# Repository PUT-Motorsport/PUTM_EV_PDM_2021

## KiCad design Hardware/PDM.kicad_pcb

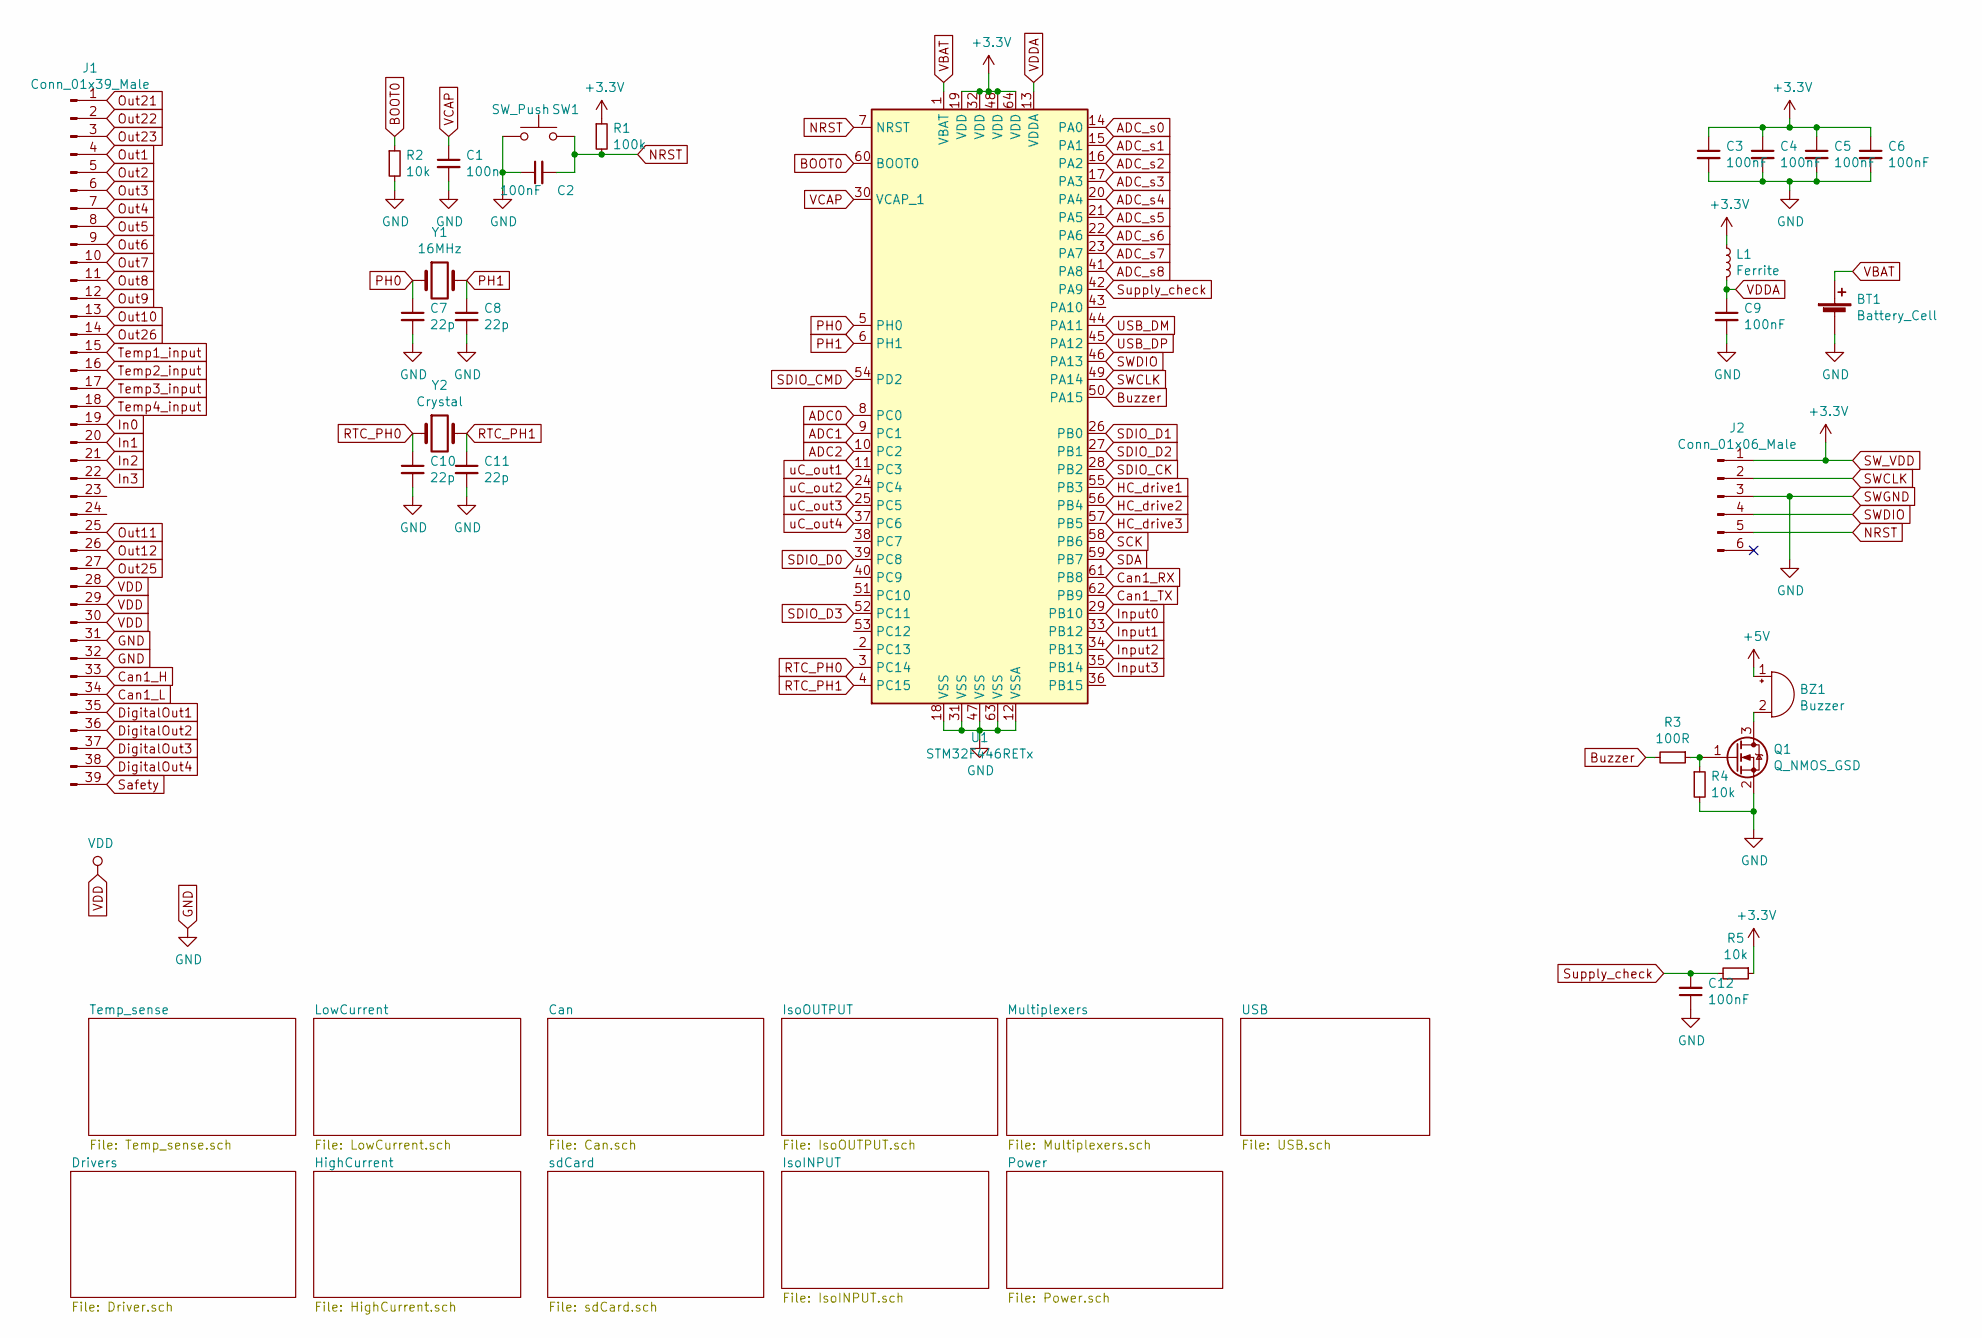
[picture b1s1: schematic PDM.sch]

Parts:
BT1: Battery_Cell; BatteryHolder_Keystone_103_1x20mm
BZ1: Buzzer; Buzzer_TDK_PS1240P02BT_D12.2mm_H6.5mm
C1: 100n; C_0603_1608Metric
C2, C3, C4, C5, C6, C9, C12: 100nF; C_0603_1608Metric
C7, C8, C10, C11: 22p; C_0603_1608Metric
J1: Conn_01x39_Male; 39pinFCI_ECU
J2: Conn_01x06_Male; PinHeader_1x06_P2.54mm_Vertical
L1: Ferrite; L_0805_2012Metric
Q1: Q_NMOS_GSD; SOT-23
R1: 100k; R_0603_1608Metric
R2, R4, R5: 10k; R_0603_1608Metric
R3: 100R; R_0603_1608Metric
SW1: SW_Push; SW_PUSH_6mm_H5mm
U1: STM32F446RETx; LQFP-64_10x10mm_P0.5mm
Y1: 16MHz; Crystal_SMD_HC49-SD
Y2: Crystal; Crystal_SMD_HC49-SD

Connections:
+5V: BZ1.1 (-); also elsewhere on the board
ADC0: U1.8 (PC0); also elsewhere on the board
ADC1: U1.9 (PC1); also elsewhere on the board
ADC2: U1.10 (PC2); also elsewhere on the board
ADC_s0: U1.14 (PA0); also elsewhere on the board
ADC_s1: U1.15 (PA1); also elsewhere on the board
ADC_s2: U1.16 (PA2); also elsewhere on the board
ADC_s3: U1.17 (PA3); also elsewhere on the board
ADC_s4: U1.20 (PA4); also elsewhere on the board
ADC_s5: U1.21 (PA5); also elsewhere on the board
ADC_s6: U1.22 (PA6); also elsewhere on the board
ADC_s7: U1.23 (PA7); also elsewhere on the board
ADC_s8: U1.41 (PA8); also elsewhere on the board
BOOT0: R2.1, U1.60 (BOOT0)
Buzzer: R3.2, U1.50 (PA15)
Can1_H: J1.33; also elsewhere on the board
Can1_L: J1.34; also elsewhere on the board
Can1_RX: U1.61 (PB8); also elsewhere on the board
Can1_TX: U1.62 (PB9); also elsewhere on the board
DigitalOut1: J1.35; also elsewhere on the board
DigitalOut2: J1.36; also elsewhere on the board
DigitalOut3: J1.37; also elsewhere on the board
DigitalOut4: J1.38; also elsewhere on the board
GND: BT1.2 (-), C1.2, C2.1, C3.2, C4.2, C5.2, C6.2, C7.2, C8.2, C9.2, C10.2, C11.2, C12.1, J1.31, J1.32, J2.3, Q1.2 (S), R2.2, R4.2, SW1.1, U1.12 (VSSA), U1.18 (VSS), U1.31 (VSS), U1.47 (VSS), U1.63 (VSS); also elsewhere on the board
HC_drive1: U1.55 (PB3); also elsewhere on the board
HC_drive2: U1.56 (PB4); also elsewhere on the board
HC_drive3: U1.57 (PB5); also elsewhere on the board
In0: J1.19; also elsewhere on the board
In1: J1.20; also elsewhere on the board
In2: J1.21; also elsewhere on the board
In3: J1.22; also elsewhere on the board
Input0: U1.29 (PB10); also elsewhere on the board
Input1: U1.33 (PB12); also elsewhere on the board
Input2: U1.34 (PB13); also elsewhere on the board
Input3: U1.35 (PB14); also elsewhere on the board
NRST: C2.2, J2.5, R1.2, SW1.2, U1.7 (NRST)
unnamed: BZ1.2 (+), Q1.3 (D)
unnamed: Q1.1 (G), R3.1, R4.1
Out1: J1.4; also elsewhere on the board
Out2: J1.5; also elsewhere on the board
Out3: J1.6; also elsewhere on the board
Out4: J1.7; also elsewhere on the board
Out5: J1.8; also elsewhere on the board
Out6: J1.9; also elsewhere on the board
Out7: J1.10; also elsewhere on the board
Out8: J1.11; also elsewhere on the board
Out9: J1.12; also elsewhere on the board
Out10: J1.13; also elsewhere on the board
Out11: J1.25; also elsewhere on the board
Out12: J1.26; also elsewhere on the board
Out21: J1.1; also elsewhere on the board
Out22: J1.2; also elsewhere on the board
Out23: J1.3; also elsewhere on the board
Out25: J1.27; also elsewhere on the board
Out26: J1.14; also elsewhere on the board
PH0: C7.1, U1.5 (PH0), Y1.1
PH1: C8.1, U1.6 (PH1), Y1.2
RTC_PH0: C10.1, U1.3 (PC14), Y2.1
RTC_PH1: C11.1, U1.4 (PC15), Y2.2
SCK: U1.58 (PB6); also elsewhere on the board
SDA: U1.59 (PB7); also elsewhere on the board
SDIO_CK: U1.28 (PB2); also elsewhere on the board
SDIO_CMD: U1.54 (PD2); also elsewhere on the board
SDIO_D0: U1.39 (PC8); also elsewhere on the board
SDIO_D1: U1.26 (PB0); also elsewhere on the board
SDIO_D2: U1.27 (PB1); also elsewhere on the board
SDIO_D3: U1.52 (PC11); also elsewhere on the board
SWCLK: J2.2, U1.49 (PA14)
SWDIO: J2.4, U1.46 (PA13)
SW_VDD: C3.1, C4.1, C5.1, C6.1, J2.1, L1.1, R1.1, R5.1, U1.19 (VDD), U1.32 (VDD), U1.48 (VDD), U1.64 (VDD); also elsewhere on the board
Safety: J1.39; also elsewhere on the board
Supply_check: C12.2, R5.2, U1.42 (PA9)
Temp1_input: J1.15; also elsewhere on the board
Temp2_input: J1.16; also elsewhere on the board
Temp3_input: J1.17; also elsewhere on the board
Temp4_input: J1.18; also elsewhere on the board
USB_DM: U1.44 (PA11); also elsewhere on the board
USB_DP: U1.45 (PA12); also elsewhere on the board
VBAT: BT1.1 (+), U1.1 (VBAT)
VCAP: C1.1, U1.30 (VCAP_1)
VDD: J1.28, J1.29, J1.30; also elsewhere on the board
VDDA: C9.1, L1.2, U1.13 (VDDA)
uC_out1: U1.11 (PC3); also elsewhere on the board
uC_out2: U1.24 (PC4); also elsewhere on the board
uC_out3: U1.25 (PC5); also elsewhere on the board
uC_out4: U1.37 (PC6); also elsewhere on the board

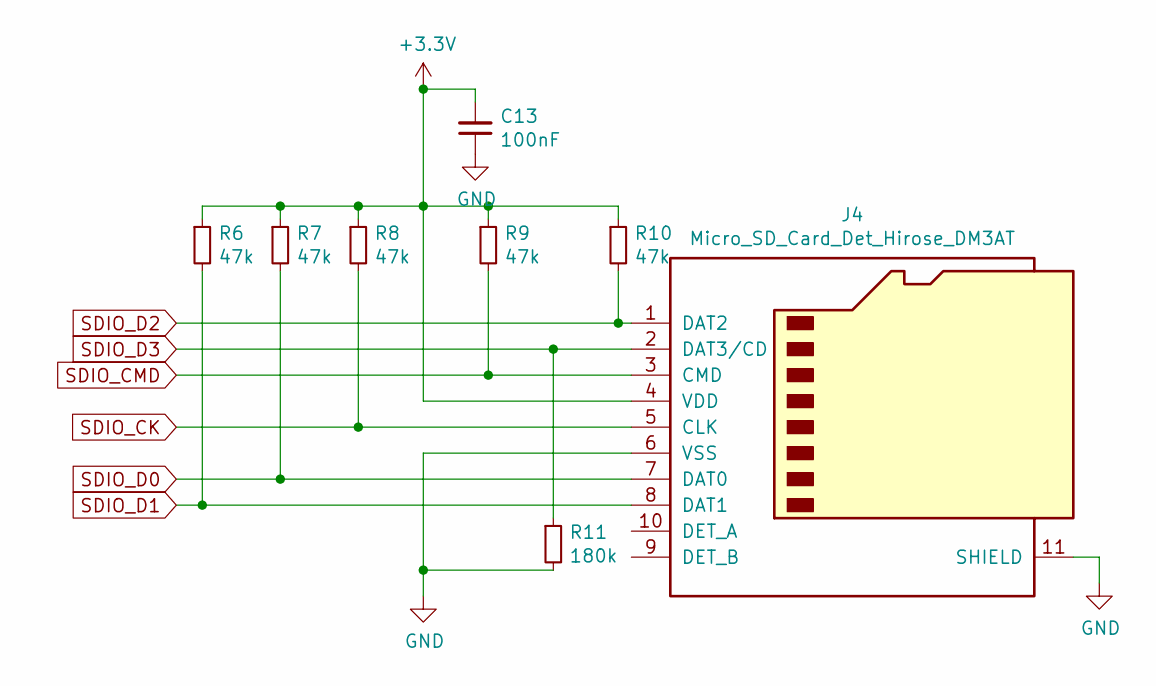
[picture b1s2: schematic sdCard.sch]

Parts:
C13: 100nF; C_0603_1608Metric
J4: Micro_SD_Card_Det_Hirose_DM3AT; microSD_HC_Hirose_DM3AT-SF-PEJM5
R6, R7, R8, R9, R10: 47k; R_0603_1608Metric
R11: 180k; R_0603_1608Metric

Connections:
GND: C13.1, J4.6 (VSS), J4.11 (SHIELD), R11.2; also elsewhere on the board
SDIO_CK: J4.5 (CLK), R8.2; also elsewhere on the board
SDIO_CMD: J4.3 (CMD), R9.2; also elsewhere on the board
SDIO_D0: J4.7 (DAT0), R7.2; also elsewhere on the board
SDIO_D1: J4.8 (DAT1), R6.2; also elsewhere on the board
SDIO_D2: J4.1 (DAT2), R10.2; also elsewhere on the board
SDIO_D3: J4.2 (DAT3/CD), R11.1; also elsewhere on the board
SW_VDD: C13.2, J4.4 (VDD), R6.1, R7.1, R8.1, R9.1, R10.1; also elsewhere on the board

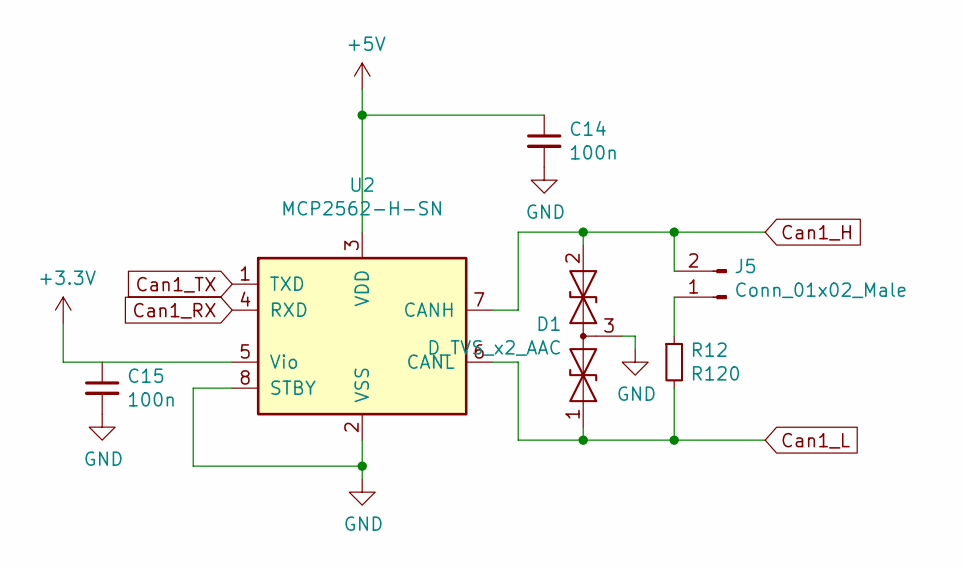
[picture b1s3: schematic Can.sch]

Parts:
C14, C15: 100n; C_0603_1608Metric
D1: D_TVS_x2_AAC; SOT-23
J5: Conn_01x02_Male; PinHeader_1x02_P2.54mm_Vertical
R12: R120; R_0603_1608Metric
U2: MCP2562-H-SN; SOIC-8_3.9x4.9mm_P1.27mm

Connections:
+5V: C14.1, U2.3 (VDD); also elsewhere on the board
Can1_H: D1.2 (A2), J5.2, U2.7 (CANH); also elsewhere on the board
Can1_L: D1.1 (A1), R12.2, U2.6 (CANL); also elsewhere on the board
Can1_RX: U2.4 (RXD); also elsewhere on the board
Can1_TX: U2.1 (TXD); also elsewhere on the board
GND: C14.2, C15.2, D1.3 (common), U2.2 (VSS), U2.8 (STBY); also elsewhere on the board
unnamed: J5.1, R12.1
SW_VDD: U2.5 (Vio); also elsewhere on the board

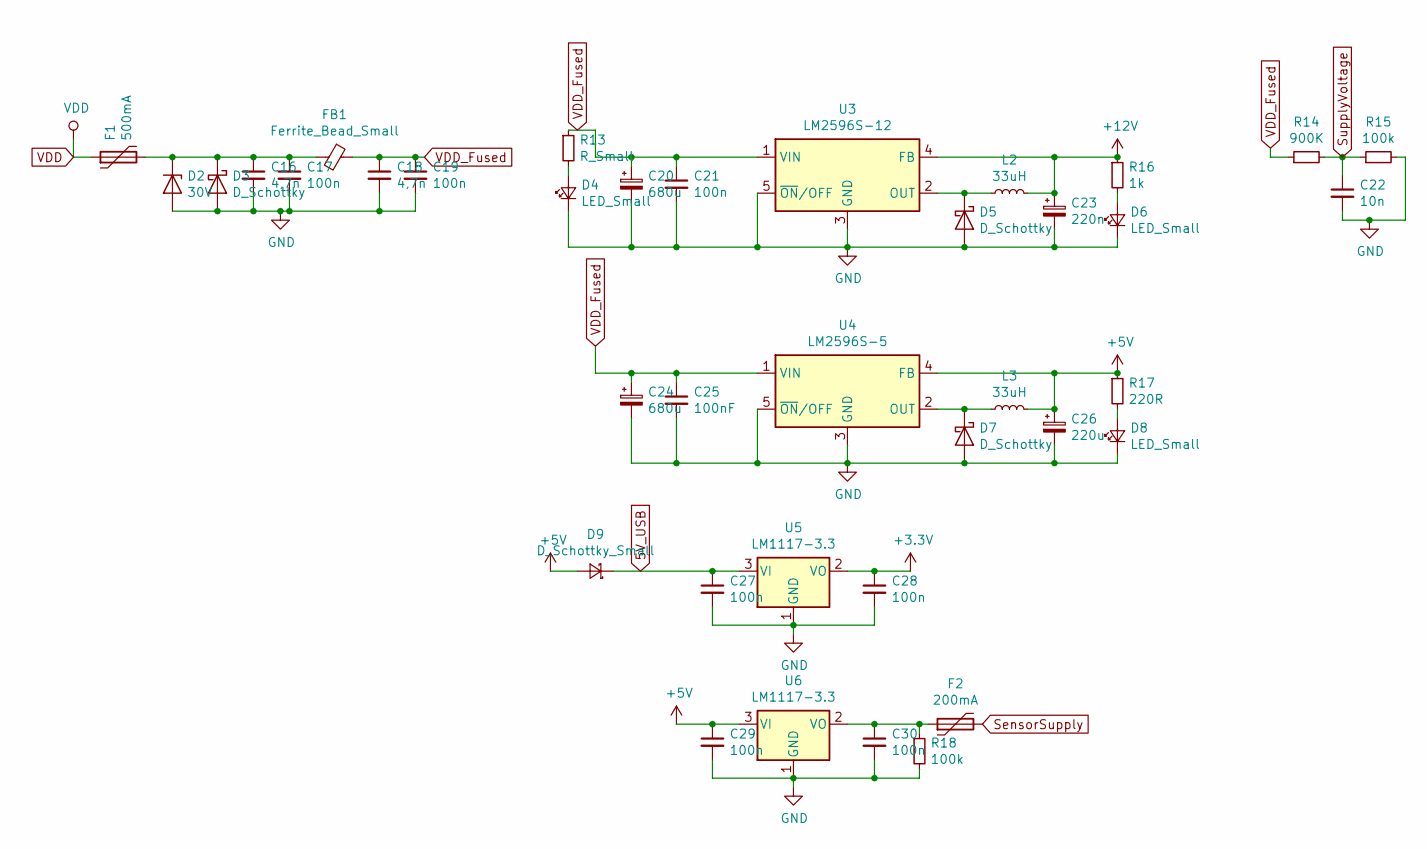
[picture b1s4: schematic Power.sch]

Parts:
C16, C18: 4,7n; C_0603_1608Metric
C17, C19, C21, C27, C28, C29, C30: 100n; C_0603_1608Metric
C20, C24: 680u; CP_Elec_8x10.5
C22: 10n; C_0603_1608Metric
C23: 220n; C_0603_1608Metric
C25: 100nF; C_0603_1608Metric
C26: 220u; CP_Elec_6.3x5.8
D2: 30V; D_SMB
D3, D5, D7: D_Schottky; D_SMB
D4, D6, D8: LED_Small; D_0805_2012Metric
D9: D_Schottky_Small; D_SMB
F1: 500mA; Fuse_1812_4532Metric
F2: 200mA; Fuse_1812_4532Metric
FB1: Ferrite_Bead_Small; L_1206_3216Metric
L2, L3: 33uH; L_12x12mm_H8mm
R13: R_Small; R_0603_1608Metric
R14: 900K; R_0603_1608Metric
R15, R18: 100k; R_0603_1608Metric
R16: 1k; R_0603_1608Metric
R17: 220R; R_0603_1608Metric
U3: LM2596S-12; TO-263-5_TabPin3
U4: LM2596S-5; TO-263-5_TabPin3
U5, U6: LM1117-3.3; SOT-223-3_TabPin2

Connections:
5V_USB: C27.1, D9.1 (K), U5.3 (VI); also elsewhere on the board
+5V: C26.1, C29.1, D9.2 (A), L3.2, R17.1, U4.4 (FB), U6.3 (VI); also elsewhere on the board
+12V: C23.1, L2.2, R16.1, U3.4 (FB); also elsewhere on the board
GND: C16.2, C17.2, C18.2, C19.2, C20.2, C21.2, C22.2, C23.2, C24.2, C25.2, C26.2, C27.2, C28.2, C29.2, C30.2, D2.2 (A), D3.2 (A), D4.1 (K), D5.2 (A), D6.1 (K), D7.2 (A), D8.1 (K), R15.2, R18.2, U3.3 (GND), U3.5 (~ON~/OFF), U4.3 (GND), U4.5 (~ON~/OFF), U5.1 (GND), U6.1 (GND); also elsewhere on the board
unnamed: C16.1, C17.1, D2.1 (K), D3.1 (K), F1.2, FB1.2
unnamed: C30.1, F2.1, R18.1, U6.2 (VO)
unnamed: D4.2 (A), R13.2
unnamed: D5.1 (K), L2.1, U3.2 (OUT)
unnamed: D6.2 (A), R16.2
unnamed: D7.1 (K), L3.1, U4.2 (OUT)
unnamed: D8.2 (A), R17.2
SW_VDD: C28.1, U5.2 (VO); also elsewhere on the board
SensorSupply: F2.2; also elsewhere on the board
SupplyVoltage: C22.1, R14.2, R15.1; also elsewhere on the board
VDD: F1.1; also elsewhere on the board
VDD_Fused: C18.1, C19.1, C20.1, C21.1, C24.1, C25.1, FB1.1, R13.1, R14.1, U3.1 (VIN), U4.1 (VIN)

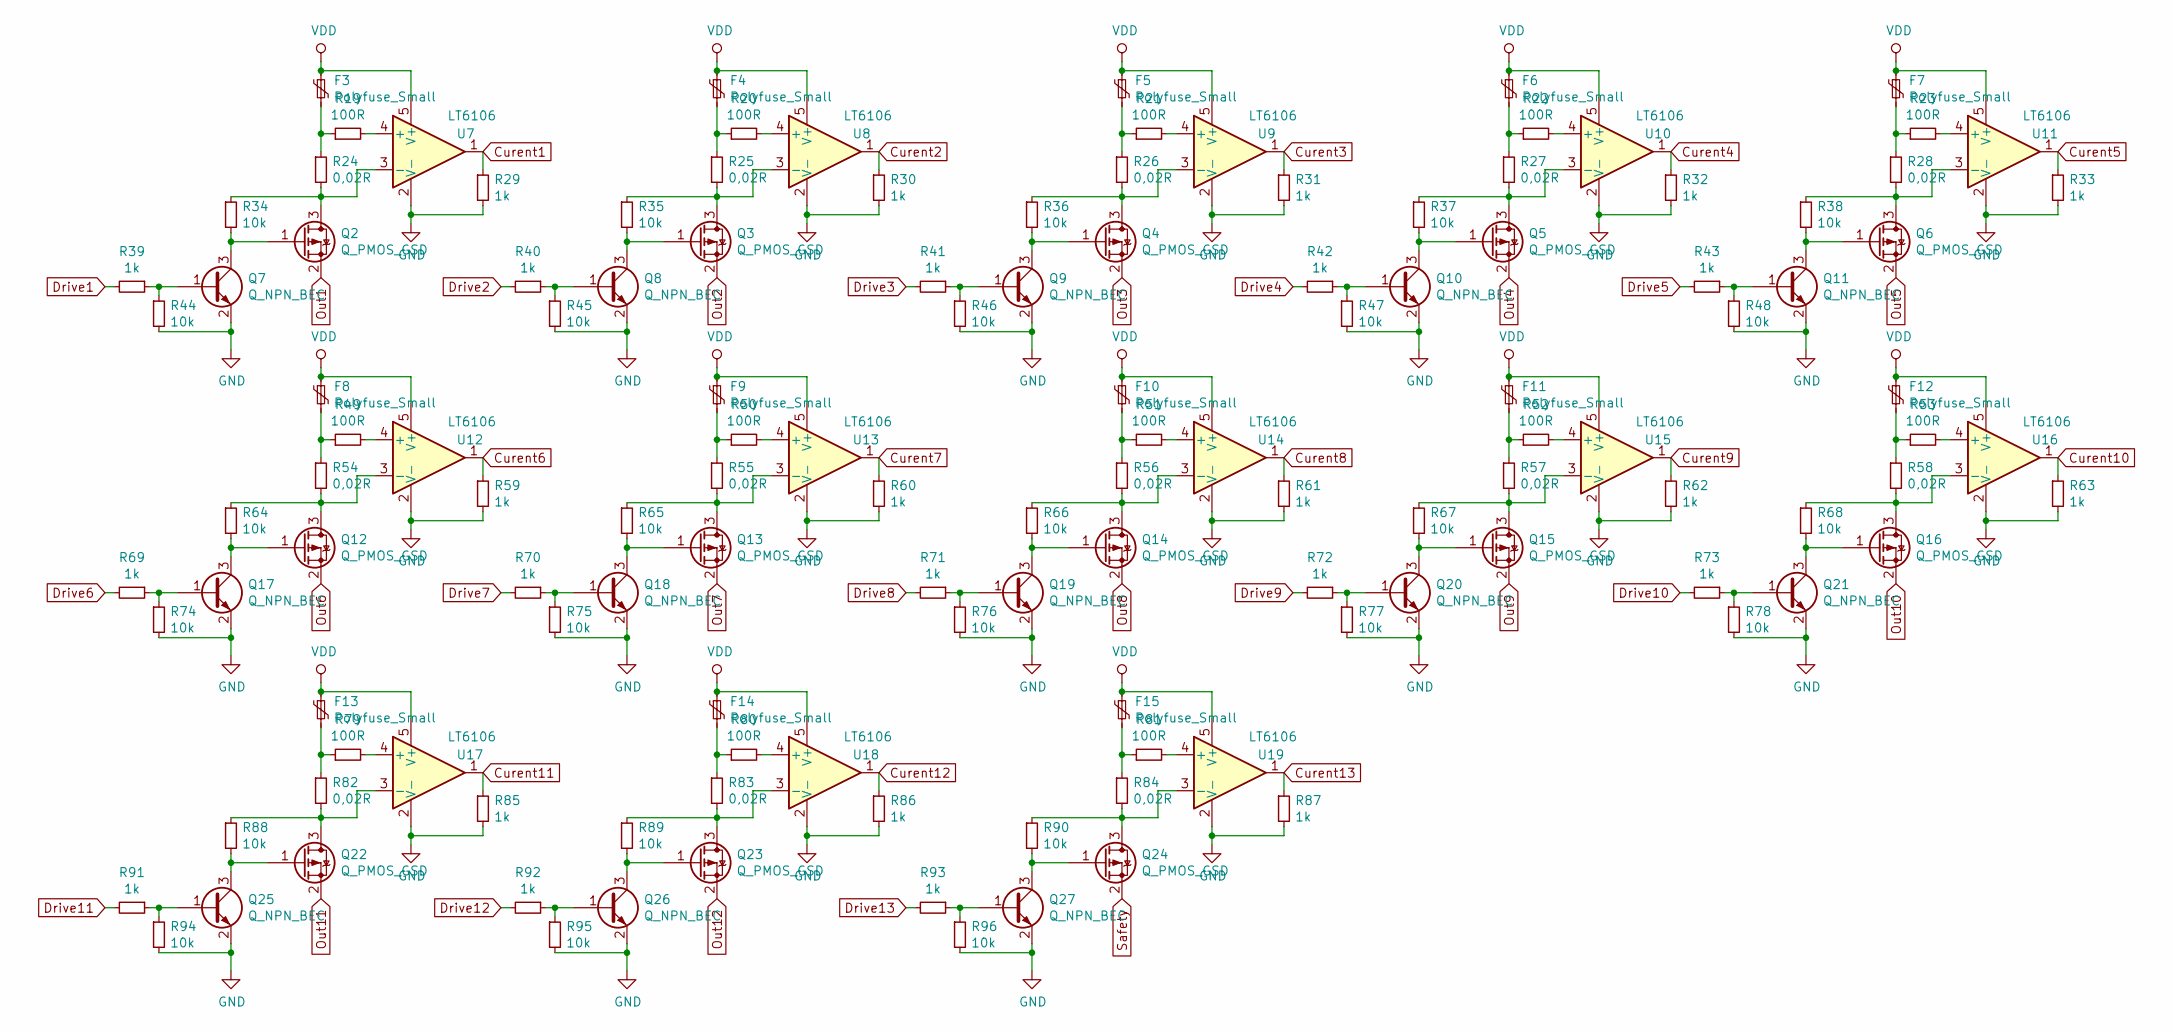
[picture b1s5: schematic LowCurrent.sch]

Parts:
F3, F4, F5, F6, F7, F8, F9, F10, F11, F12, F13, F14, F15: Polyfuse_Small; Fuse_1812_4532Metric
Q2, Q3, Q4, Q5, Q6, Q12, Q13, Q14, Q15, Q16, Q22, Q23, Q24: Q_PMOS_GSD; PowerIntegrations_SO-8
Q7, Q8, Q9, Q10, Q11, Q17, Q18, Q19, Q20, Q21: Q_NPN_BEC; SOT-23
Q25, Q26, Q27: Q_NPN_BEC; SOT-23-5
R19, R20, R21, R22, R23, R49, R50, R51, R52, R53, R79, R80, R81: 100R; R_0603_1608Metric
R24, R25, R26, R27, R28, R54, R55, R56, R57, R58, R82, R83, R84: 0,02R; R_2512_6332Metric
R29, R30, R31, R32, R33, R39, R40, R41, R42, R43, R59, R60, R61, R62, R63, R69, R70, R71, R72, R73, R85, R86, R87, R91, R92, R93: 1k; R_0603_1608Metric
R34, R35, R36, R37, R38, R44, R45, R46, R47, R48, R64, R65, R66, R67, R68, R74, R75, R76, R77, R78, R88, R89, R90, R94, R95, R96: 10k; R_0603_1608Metric
U7, U8, U9, U10, U11, U12, U13, U14, U15, U16, U17, U18, U19: LT6106; SOT-23-5

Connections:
Curent1: R29.1, U7.1; also elsewhere on the board
Curent2: R30.1, U8.1; also elsewhere on the board
Curent3: R31.1, U9.1; also elsewhere on the board
Curent4: R32.1, U10.1; also elsewhere on the board
Curent5: R33.1, U11.1; also elsewhere on the board
Curent6: R59.1, U12.1; also elsewhere on the board
Curent7: R60.1, U13.1; also elsewhere on the board
Curent8: R61.1, U14.1; also elsewhere on the board
Curent9: R62.1, U15.1; also elsewhere on the board
Curent10: R63.1, U16.1; also elsewhere on the board
Curent11: R85.1, U17.1; also elsewhere on the board
Curent12: R86.1, U18.1; also elsewhere on the board
Curent13: R87.1, U19.1; also elsewhere on the board
Drive1: R39.2; also elsewhere on the board
Drive2: R40.2; also elsewhere on the board
Drive3: R41.2; also elsewhere on the board
Drive4: R42.2; also elsewhere on the board
Drive5: R43.2; also elsewhere on the board
Drive6: R69.2; also elsewhere on the board
Drive7: R70.2; also elsewhere on the board
Drive8: R71.2; also elsewhere on the board
Drive9: R72.2; also elsewhere on the board
Drive10: R73.2; also elsewhere on the board
Drive11: R91.2; also elsewhere on the board
Drive12: R92.2; also elsewhere on the board
Drive13: R93.2; also elsewhere on the board
GND: Q7.2 (E), Q8.2 (E), Q9.2 (E), Q10.2 (E), Q11.2 (E), Q17.2 (E), Q18.2 (E), Q19.2 (E), Q20.2 (E), Q21.2 (E), Q25.2 (E), Q26.2 (E), Q27.2 (E), R29.2, R30.2, R31.2, R32.2, R33.2, R44.2, R45.2, R46.2, R47.2, R48.2, R59.2, R60.2, R61.2, R62.2, R63.2, R74.2, R75.2, R76.2, R77.2, R78.2, R85.2, R86.2, R87.2, R94.2, R95.2, R96.2, U7.2 (V-), U8.2 (V-), U9.2 (V-), U10.2 (V-), U11.2 (V-), U12.2 (V-), U13.2 (V-), U14.2 (V-), U15.2 (V-), U16.2 (V-), U17.2 (V-), U18.2 (V-), U19.2 (V-); also elsewhere on the board
unnamed: F3.2, R19.1, R24.1
unnamed: F4.2, R20.1, R25.1
unnamed: F5.2, R21.1, R26.1
unnamed: F6.2, R22.1, R27.1
unnamed: F7.2, R23.1, R28.1
unnamed: F8.2, R49.1, R54.1
unnamed: F9.2, R50.1, R55.1
unnamed: F10.2, R51.1, R56.1
unnamed: F11.2, R52.1, R57.1
unnamed: F12.2, R53.1, R58.1
unnamed: F13.2, R79.1, R82.1
unnamed: F14.2, R80.1, R83.1
unnamed: F15.2, R81.1, R84.1
unnamed: Q2.1 (G), Q7.3 (C), R34.2
unnamed: Q2.3 (D), R24.2, R34.1, U7.3 (-)
unnamed: Q3.1 (G), Q8.3 (C), R35.2
unnamed: Q3.3 (D), R25.2, R35.1, U8.3 (-)
unnamed: Q4.1 (G), Q9.3 (C), R36.2
unnamed: Q4.3 (D), R26.2, R36.1, U9.3 (-)
unnamed: Q5.3 (D), R27.2, R37.1, U10.3 (-)
unnamed: Q6.3 (D), R28.2, R38.1, U11.3 (-)
unnamed: Q7.1 (B), R39.1, R44.1
unnamed: Q8.1 (B), R40.1, R45.1
unnamed: Q9.1 (B), R41.1, R46.1
unnamed: Q10.1 (B), R42.1, R47.1
unnamed: Q5.1 (G), Q10.3 (C), R37.2
unnamed: Q11.1 (B), R43.1, R48.1
unnamed: Q6.1 (G), Q11.3 (C), R38.2
unnamed: Q12.1 (G), Q17.3 (C), R64.2
unnamed: Q12.3 (D), R54.2, R64.1, U12.3 (-)
unnamed: Q13.1 (G), Q18.3 (C), R65.2
unnamed: Q13.3 (D), R55.2, R65.1, U13.3 (-)
unnamed: Q14.1 (G), Q19.3 (C), R66.2
unnamed: Q14.3 (D), R56.2, R66.1, U14.3 (-)
unnamed: Q15.1 (G), Q20.3 (C), R67.2
unnamed: Q15.3 (D), R57.2, R67.1, U15.3 (-)
unnamed: Q16.1 (G), Q21.3 (C), R68.2
unnamed: Q16.3 (D), R58.2, R68.1, U16.3 (-)
unnamed: Q17.1 (B), R69.1, R74.1
unnamed: Q18.1 (B), R70.1, R75.1
unnamed: Q19.1 (B), R71.1, R76.1
unnamed: Q20.1 (B), R72.1, R77.1
unnamed: Q21.1 (B), R73.1, R78.1
unnamed: Q22.1 (G), Q25.3 (C), R88.2
unnamed: Q22.3 (D), R82.2, R88.1, U17.3 (-)
unnamed: Q23.1 (G), Q26.3 (C), R89.2
unnamed: Q23.3 (D), R83.2, R89.1, U18.3 (-)
unnamed: Q24.1 (G), Q27.3 (C), R90.2
unnamed: Q24.3 (D), R84.2, R90.1, U19.3 (-)
unnamed: Q25.1 (B), R91.1, R94.1
unnamed: Q26.1 (B), R92.1, R95.1
unnamed: Q27.1 (B), R93.1, R96.1
unnamed: R19.2, U7.4 (+)
unnamed: R20.2, U8.4 (+)
unnamed: R21.2, U9.4 (+)
unnamed: R22.2, U10.4 (+)
unnamed: R23.2, U11.4 (+)
unnamed: R49.2, U12.4 (+)
unnamed: R50.2, U13.4 (+)
unnamed: R51.2, U14.4 (+)
unnamed: R52.2, U15.4 (+)
unnamed: R53.2, U16.4 (+)
unnamed: R79.2, U17.4 (+)
unnamed: R80.2, U18.4 (+)
unnamed: R81.2, U19.4 (+)
Out1: Q2.2 (S); also elsewhere on the board
Out2: Q3.2 (S); also elsewhere on the board
Out3: Q4.2 (S); also elsewhere on the board
Out4: Q5.2 (S); also elsewhere on the board
Out5: Q6.2 (S); also elsewhere on the board
Out6: Q12.2 (S); also elsewhere on the board
Out7: Q13.2 (S); also elsewhere on the board
Out8: Q14.2 (S); also elsewhere on the board
Out9: Q15.2 (S); also elsewhere on the board
Out10: Q16.2 (S); also elsewhere on the board
Out11: Q22.2 (S); also elsewhere on the board
Out12: Q23.2 (S); also elsewhere on the board
Safety: Q24.2 (S); also elsewhere on the board
VDD: F3.1, F4.1, F5.1, F6.1, F7.1, F8.1, F9.1, F10.1, F11.1, F12.1, F13.1, F14.1, F15.1, U7.5 (V+), U8.5 (V+), U9.5 (V+), U10.5 (V+), U11.5 (V+), U12.5 (V+), U13.5 (V+), U14.5 (V+), U15.5 (V+), U16.5 (V+), U17.5 (V+), U18.5 (V+), U19.5 (V+); also elsewhere on the board

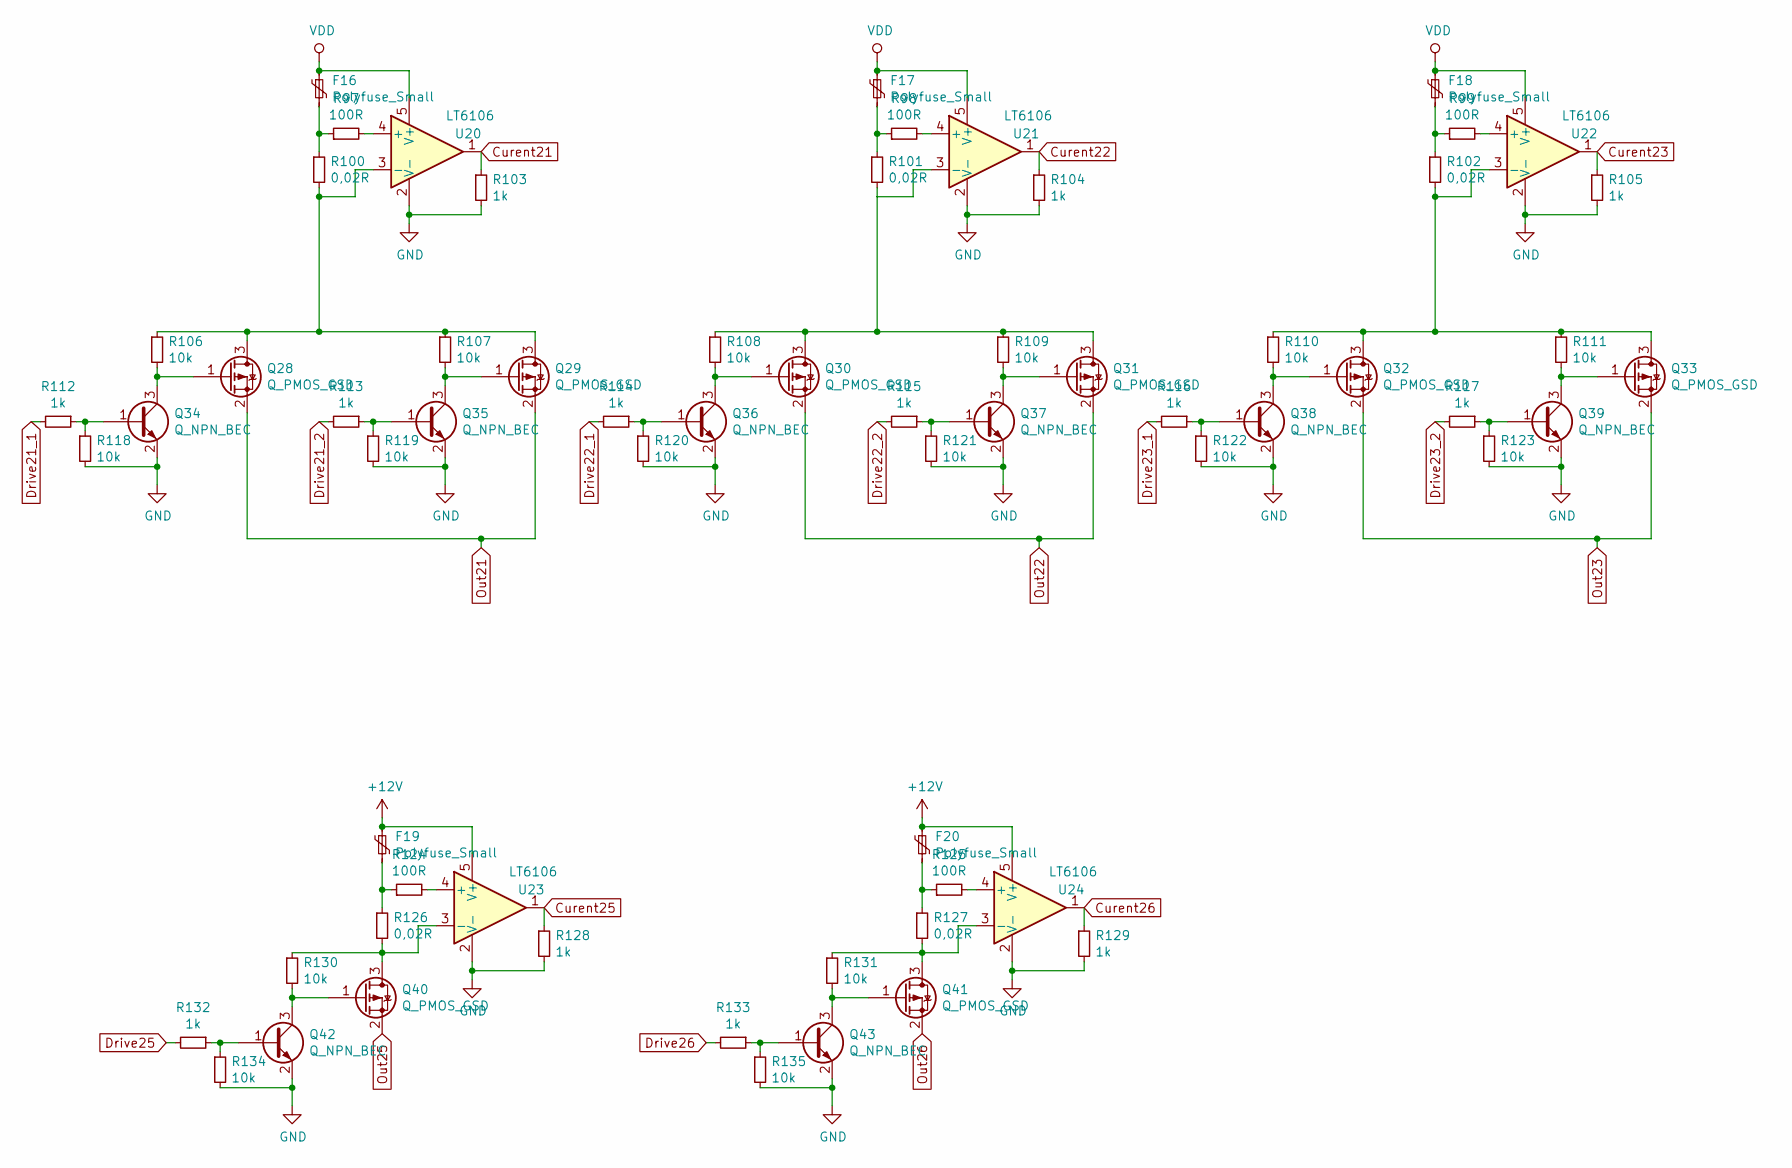
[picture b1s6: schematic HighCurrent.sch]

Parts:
F16, F17, F18, F19, F20: Polyfuse_Small; Fuse_1812_4532Metric
Q28, Q29, Q30, Q31, Q32, Q33, Q40, Q41: Q_PMOS_GSD; PowerIntegrations_SO-8
Q34, Q35, Q36, Q37, Q38, Q39, Q42, Q43: Q_NPN_BEC; SOT-23
R97, R98, R99, R124, R125: 100R; R_0603_1608Metric
R100, R101, R102, R126, R127: 0,02R; R_2512_6332Metric
R103, R104, R105, R112, R113, R114, R115, R116, R117, R128, R129, R132, R133: 1k; R_0603_1608Metric
R106, R107, R108, R109, R110, R111, R118, R119, R120, R121, R122, R123, R130, R131, R134, R135: 10k; R_0603_1608Metric
U20, U21, U22, U23, U24: LT6106; SOT-23-5

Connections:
+12V: F19.1, F20.1, U23.5 (V+), U24.5 (V+); also elsewhere on the board
Curent21: R103.1, U20.1; also elsewhere on the board
Curent22: R104.1, U21.1; also elsewhere on the board
Curent23: R105.1, U22.1; also elsewhere on the board
Curent25: R128.1, U23.1; also elsewhere on the board
Curent26: R129.1, U24.1; also elsewhere on the board
Drive21_1: R112.2, R113.2; also elsewhere on the board
Drive22_1: R114.2, R115.2; also elsewhere on the board
Drive23_1: R116.2, R117.2; also elsewhere on the board
Drive25: R132.2; also elsewhere on the board
Drive26: R133.2; also elsewhere on the board
GND: Q34.2 (E), Q35.2 (E), Q36.2 (E), Q37.2 (E), Q38.2 (E), Q39.2 (E), Q42.2 (E), Q43.2 (E), R103.2, R104.2, R105.2, R118.2, R119.2, R120.2, R121.2, R122.2, R123.2, R128.2, R129.2, R134.2, R135.2, U20.2 (V-), U21.2 (V-), U22.2 (V-), U23.2 (V-), U24.2 (V-); also elsewhere on the board
unnamed: F16.2, R97.1, R100.1
unnamed: F17.2, R98.1, R101.1
unnamed: F18.2, R99.1, R102.1
unnamed: F19.2, R124.1, R126.1
unnamed: F20.2, R125.1, R127.1
unnamed: Q28.1 (G), Q34.3 (C), R106.2
unnamed: Q28.3 (D), Q29.3 (D), R100.2, R106.1, R107.1, U20.3 (-)
unnamed: Q29.1 (G), Q35.3 (C), R107.2
unnamed: Q30.1 (G), Q36.3 (C), R108.2
unnamed: Q30.3 (D), Q31.3 (D), R101.2, R108.1, R109.1, U21.3 (-)
unnamed: Q31.1 (G), Q37.3 (C), R109.2
unnamed: Q32.1 (G), Q38.3 (C), R110.2
unnamed: Q32.3 (D), Q33.3 (D), R102.2, R110.1, R111.1, U22.3 (-)
unnamed: Q33.1 (G), Q39.3 (C), R111.2
unnamed: Q34.1 (B), R112.1, R118.1
unnamed: Q35.1 (B), R113.1, R119.1
unnamed: Q36.1 (B), R114.1, R120.1
unnamed: Q37.1 (B), R115.1, R121.1
unnamed: Q38.1 (B), R116.1, R122.1
unnamed: Q39.1 (B), R117.1, R123.1
unnamed: Q40.1 (G), Q42.3 (C), R130.2
unnamed: Q40.3 (D), R126.2, R130.1, U23.3 (-)
unnamed: Q41.1 (G), Q43.3 (C), R131.2
unnamed: Q41.3 (D), R127.2, R131.1, U24.3 (-)
unnamed: Q42.1 (B), R132.1, R134.1
unnamed: Q43.1 (B), R133.1, R135.1
unnamed: R97.2, U20.4 (+)
unnamed: R98.2, U21.4 (+)
unnamed: R99.2, U22.4 (+)
unnamed: R124.2, U23.4 (+)
unnamed: R125.2, U24.4 (+)
Out21: Q28.2 (S), Q29.2 (S); also elsewhere on the board
Out22: Q30.2 (S), Q31.2 (S); also elsewhere on the board
Out23: Q32.2 (S), Q33.2 (S); also elsewhere on the board
Out25: Q40.2 (S); also elsewhere on the board
Out26: Q41.2 (S); also elsewhere on the board
VDD: F16.1, F17.1, F18.1, U20.5 (V+), U21.5 (V+), U22.5 (V+); also elsewhere on the board

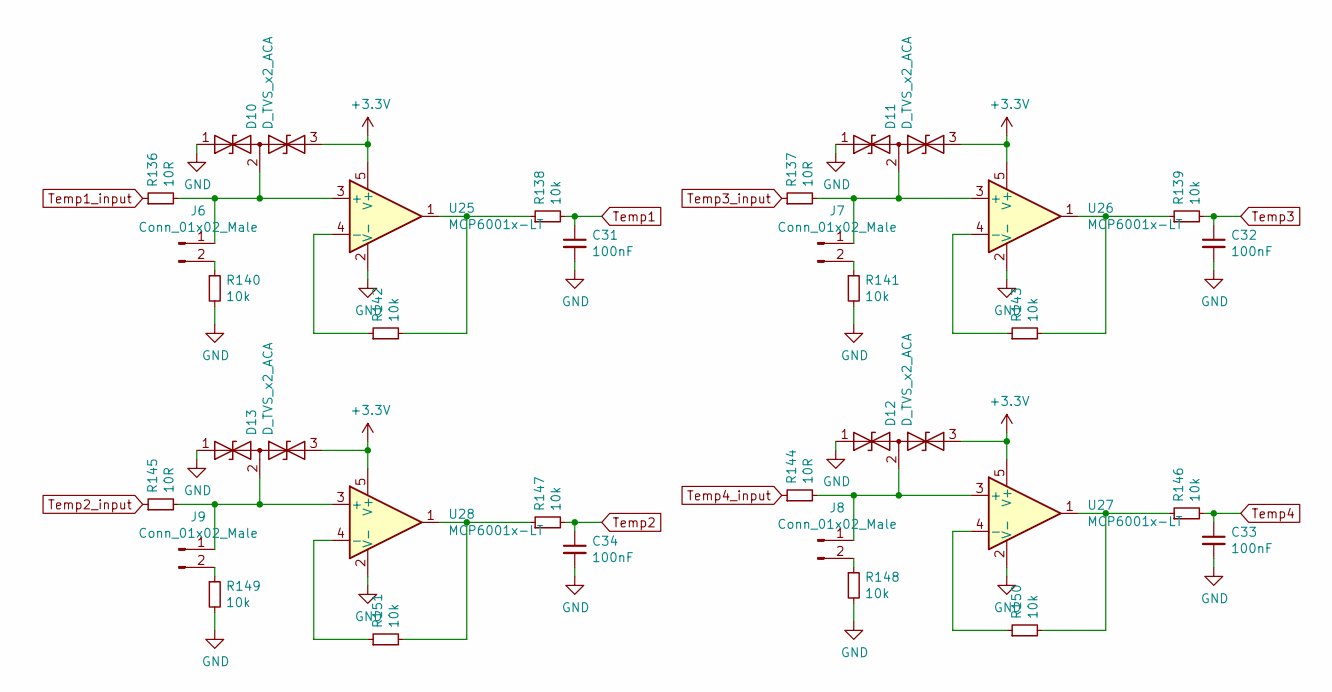
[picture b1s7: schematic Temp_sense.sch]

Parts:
C31, C32, C33, C34: 100nF; C_0603_1608Metric
D10, D11, D12, D13: D_TVS_x2_ACA; SOT-23
J6, J7, J8, J9: Conn_01x02_Male; PinHeader_1x02_P2.54mm_Vertical
R136, R137, R144, R145: 10R; R_0603_1608Metric
R138, R139, R140, R141, R142, R143, R146, R147, R148, R149, R150, R151: 10k; R_0603_1608Metric
U25, U26, U27, U28: MCP6001x-LT; SOT-353_SC-70-5

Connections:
GND: C31.2, C32.2, C33.2, C34.2, D10.1 (A1), D11.1 (A1), D12.1 (A1), D13.1 (A1), R140.2, R141.2, R148.2, R149.2, U25.2 (V-), U26.2 (V-), U27.2 (V-), U28.2 (V-); also elsewhere on the board
unnamed: D10.2 (common), J6.1, R136.2, U25.3 (+)
unnamed: D11.2 (common), J7.1, R137.2, U26.3 (+)
unnamed: D12.2 (common), J8.1, R144.2, U27.3 (+)
unnamed: D13.2 (common), J9.1, R145.2, U28.3 (+)
unnamed: J6.2, R140.1
unnamed: J7.2, R141.1
unnamed: J8.2, R148.1
unnamed: J9.2, R149.1
unnamed: R138.1, R142.2, U25.1
unnamed: R139.1, R143.2, U26.1
unnamed: R142.1, U25.4 (-)
unnamed: R143.1, U26.4 (-)
unnamed: R146.1, R150.2, U27.1
unnamed: R147.1, R151.2, U28.1
unnamed: R150.1, U27.4 (-)
unnamed: R151.1, U28.4 (-)
SW_VDD: D10.3 (A2), D11.3 (A2), D12.3 (A2), D13.3 (A2), U25.5 (V+), U26.5 (V+), U27.5 (V+), U28.5 (V+); also elsewhere on the board
Temp1: C31.1, R138.2; also elsewhere on the board
Temp1_input: R136.1; also elsewhere on the board
Temp2: C34.1, R147.2; also elsewhere on the board
Temp2_input: R145.1; also elsewhere on the board
Temp3: C32.1, R139.2; also elsewhere on the board
Temp3_input: R137.1; also elsewhere on the board
Temp4: C33.1, R146.2; also elsewhere on the board
Temp4_input: R144.1; also elsewhere on the board

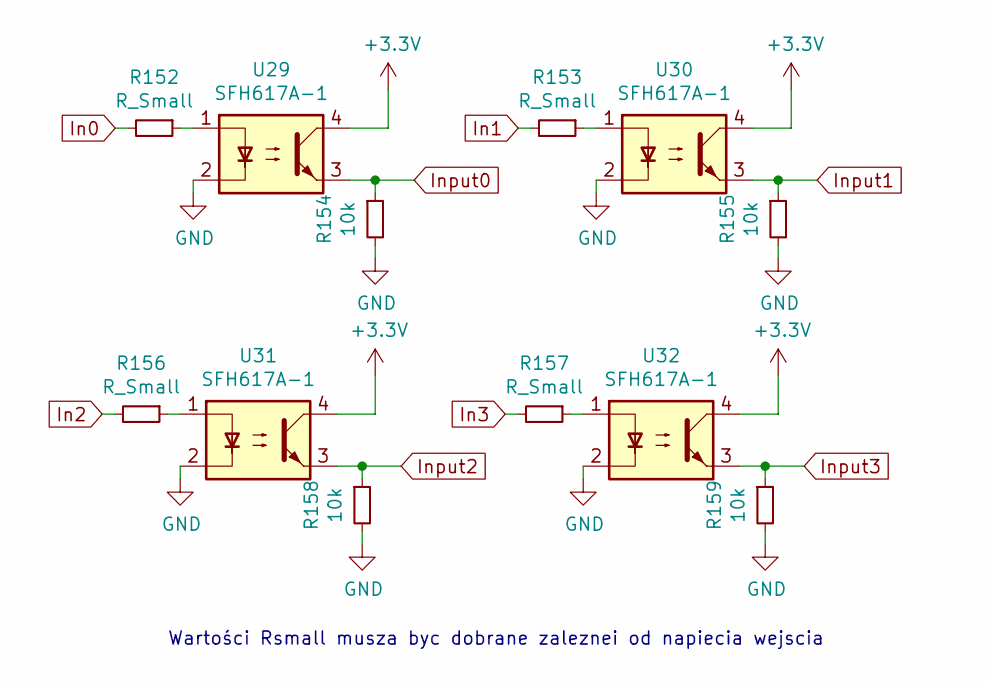
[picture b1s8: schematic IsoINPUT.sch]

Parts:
R152, R153, R156, R157: R_Small; R_0603_1608Metric
R154, R155, R158, R159: 10k; R_0603_1608Metric
U29, U30, U31, U32: SFH617A-1; DIP-4_W7.62mm

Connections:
GND: R154.2, R155.2, R158.2, R159.2, U29.2, U30.2, U31.2, U32.2; also elsewhere on the board
In0: R152.2; also elsewhere on the board
In1: R153.2; also elsewhere on the board
In2: R156.2; also elsewhere on the board
In3: R157.2; also elsewhere on the board
Input0: R154.1, U29.3; also elsewhere on the board
Input1: R155.1, U30.3; also elsewhere on the board
Input2: R158.1, U31.3; also elsewhere on the board
Input3: R159.1, U32.3; also elsewhere on the board
unnamed: R152.1, U29.1
unnamed: R153.1, U30.1
unnamed: R156.1, U31.1
unnamed: R157.1, U32.1
SW_VDD: U29.4, U30.4, U31.4, U32.4; also elsewhere on the board

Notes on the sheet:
Wartości Rsmall musza byc dobrane zaleznei od napiecia wejscia

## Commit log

2021-04-15 Added project files
    Added project files which are previously developed locally
2021-04-15 Deleted unused file to match gitignore requirements
2021-04-24 passive components changed to 0603 and Main connector configuration set
